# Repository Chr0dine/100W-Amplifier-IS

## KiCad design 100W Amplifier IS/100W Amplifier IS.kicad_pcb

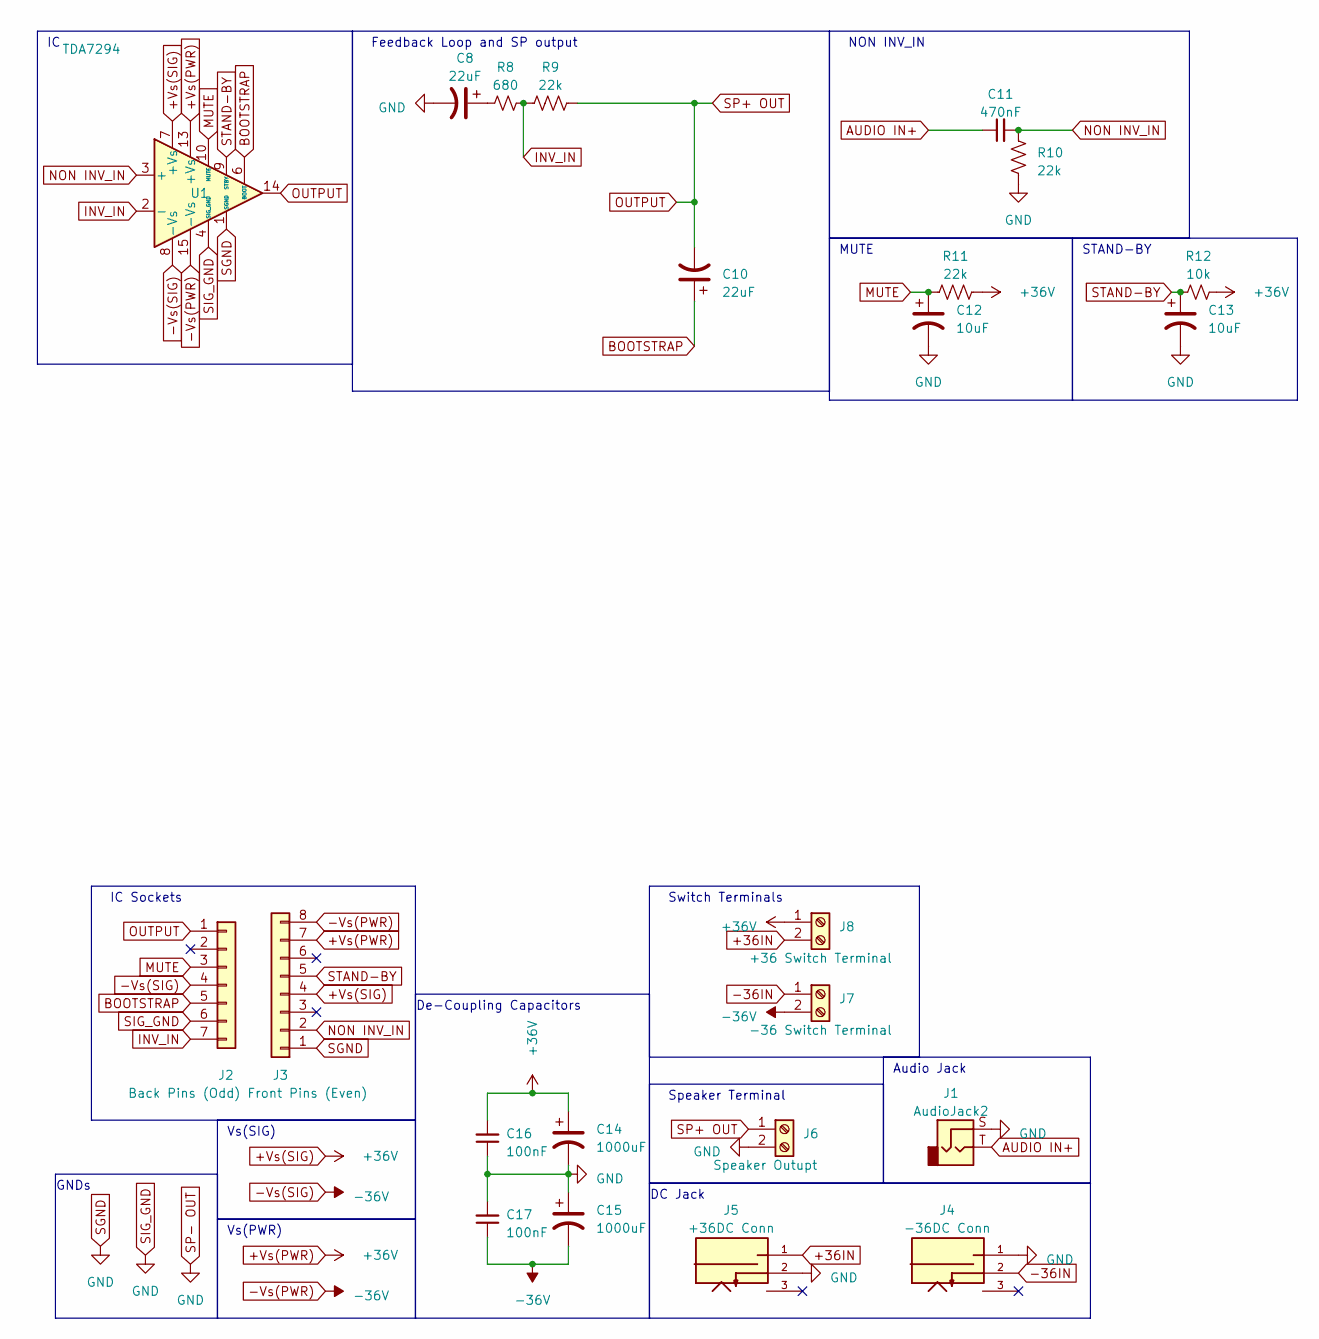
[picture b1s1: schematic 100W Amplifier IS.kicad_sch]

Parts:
C8, C10: 22uF; CP_Radial_D10.0mm_P5.00mm
C11: 470nF; C_Disc_D5.0mm_W2.5mm_P5.00mm
C12, C13: 10uF; CP_Radial_D8.0mm_P3.50mm
C14, C15: 1000uF; CP_Radial_D16.0mm_P7.50mm
C16, C17: 100nF; C_Disc_D5.0mm_W2.5mm_P5.00mm
J1: AudioJack2; Jack_3.5mm_CUI_SJ1-3523N_Horizontal
J2: Back Pins (Odd); PinSocket_1x07_P2.54mm_Vertical
J3: Front Pins (Even); PinSocket_1x08_P2.54mm_Vertical
J4: -36DC Conn; GRAVITECH_CON-SOCJ-2155; PARTREV NA
J5: +36DC Conn; GRAVITECH_CON-SOCJ-2155; PARTREV NA
J6: Speaker Outupt; TerminalBlock_Altech_AK300-2_P5.00mm
J7: -36 Switch Terminal; TerminalBlock_Altech_AK300-2_P5.00mm
J8: +36 Switch Terminal; TerminalBlock_Altech_AK300-2_P5.00mm
R8: 680; R_Axial_DIN0207_L6.3mm_D2.5mm_P10.16mm_Horizontal
R9, R10, R11: 22k; R_Axial_DIN0207_L6.3mm_D2.5mm_P10.16mm_Horizontal
R12: 10k; R_Axial_DIN0207_L6.3mm_D2.5mm_P10.16mm_Horizontal
U1: TDA7294

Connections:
+36IN: J5.1, J8.2
+Vs(PWR): C14.1, C16.2, J3.4, J3.7, J8.1, R11.1, R12.1, U1.7 (+Vs), U1.13 (+Vs)
-36IN: J4.2, J7.1
-Vs(PWR): C15.2, C17.1, J2.4, J3.8, J7.2, U1.8 (-Vs), U1.15 (-Vs)
AUDIO IN+: C11.1, J1.T
BOOTSTRAP: C10.1, J2.5, U1.6 (BOOT)
INV_IN: J2.7, R8.2, R9.1, U1.2 (-)
MUTE: C12.1, J2.3, R11.2, U1.10 (MUTE)
NON INV_IN: C11.2, J3.2, R10.2, U1.3 (+)
unnamed: C8.1, R8.1
OUTPUT: C10.2, J2.1, J6.1, R9.2, U1.14
SGND: C8.2, C12.2, C13.2, C14.2, C15.1, C16.1, C17.2, J1.S, J2.6, J3.1, J4.1, J5.2, J6.2, R10.1, U1.1 (SGND), U1.4 (SIG_GND)
STAND-BY: C13.1, J3.5, R12.2, U1.9 (STBY)

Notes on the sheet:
Vs(PWR)
DC Jack
GNDs
MUTE
Switch Terminals
STAND-BY
NON INV_IN
Speaker Terminal
Audio Jack
De-Coupling Capacitors
IC Sockets
Feedback Loop and SP output
Vs(SIG)

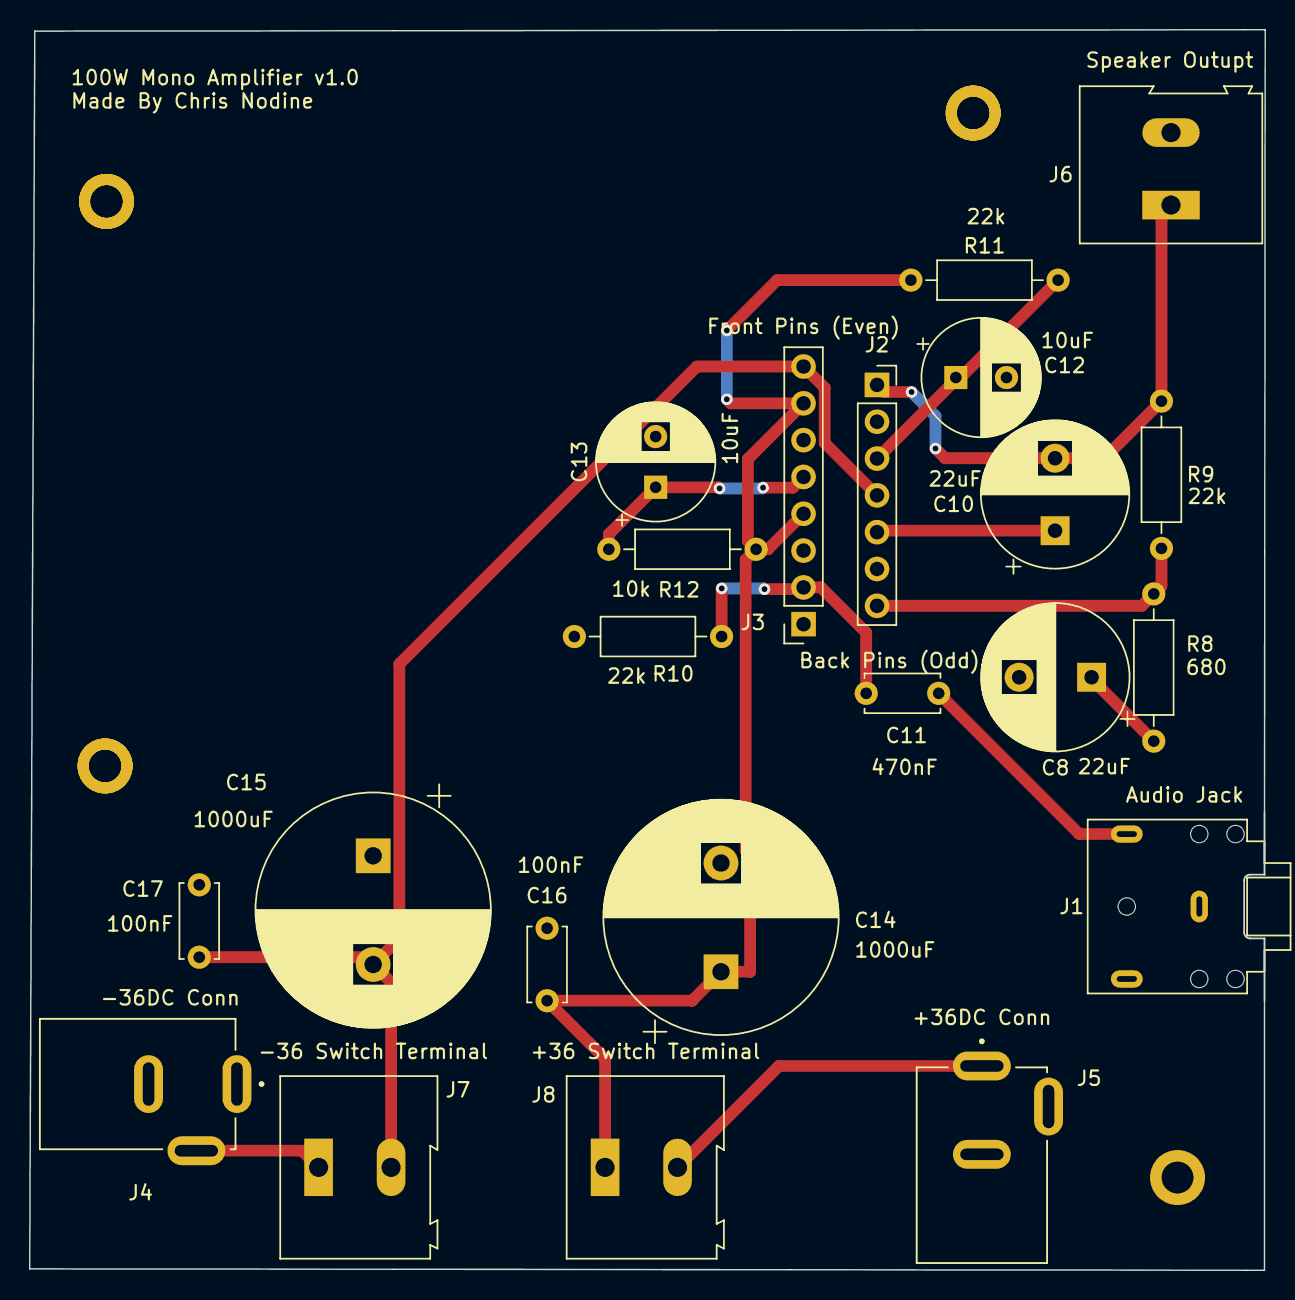
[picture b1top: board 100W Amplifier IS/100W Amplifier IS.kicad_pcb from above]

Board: 2 copper layers, 85.2 x 85.6 mm, 22 parts (0 on the bottom side), 13 nets.

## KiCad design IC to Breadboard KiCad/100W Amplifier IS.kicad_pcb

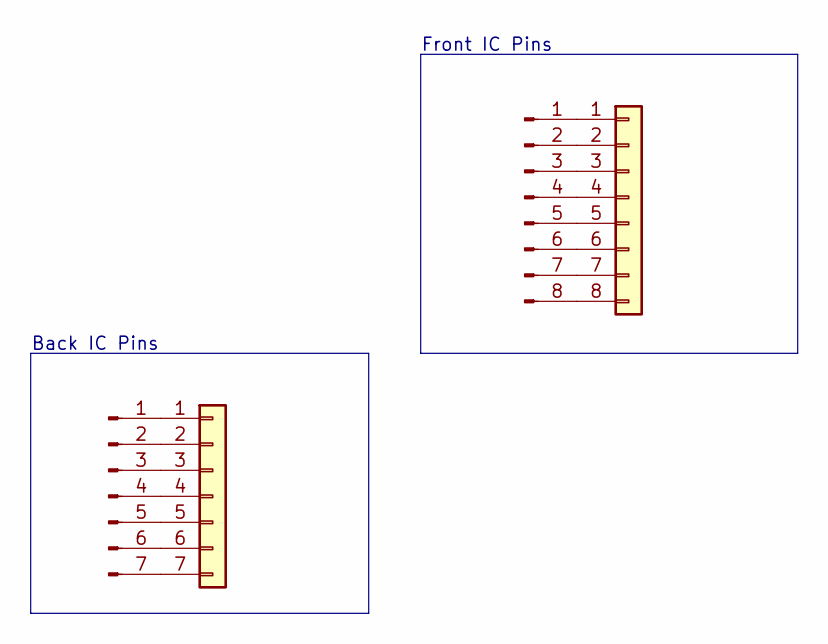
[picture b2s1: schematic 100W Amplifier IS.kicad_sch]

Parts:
J1: Conn_01x08; PinSocket_1x08_P2.54mm_Vertical
J2: Conn_01x07_Pin; PinHeader_1x07_P2.54mm_Vertical
J3: Conn_01x08_Pin; PinHeader_1x08_P2.54mm_Vertical
J4: Conn_01x07; PinSocket_1x07_P2.54mm_Vertical

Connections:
unnamed: J1.1, J3.1
unnamed: J1.2, J3.2
unnamed: J1.3, J3.3
unnamed: J1.4, J3.4
unnamed: J1.5, J3.5
unnamed: J1.6, J3.6
unnamed: J1.7, J3.7
unnamed: J1.8, J3.8
unnamed: J2.1, J4.1
unnamed: J2.2, J4.2
unnamed: J2.3, J4.3
unnamed: J2.4, J4.4
unnamed: J2.5, J4.5
unnamed: J2.6, J4.6
unnamed: J2.7, J4.7

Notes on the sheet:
Back IC Pins
Front IC Pins

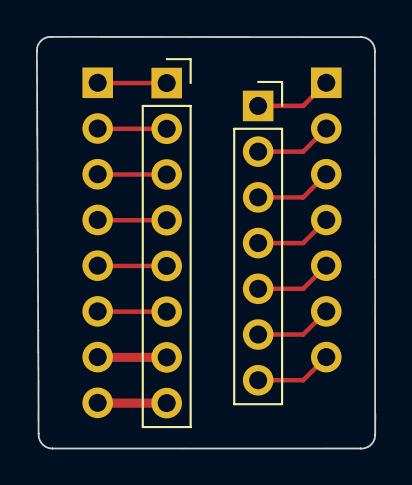
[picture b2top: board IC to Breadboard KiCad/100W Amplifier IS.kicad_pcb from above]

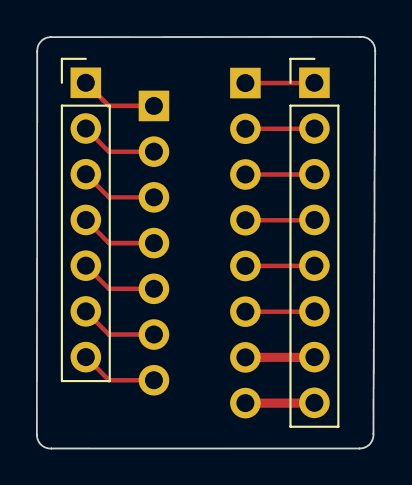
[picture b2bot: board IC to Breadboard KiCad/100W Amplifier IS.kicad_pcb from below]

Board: 2 copper layers, 18.8 x 22.9 mm, 4 parts (2 on the bottom side), 15 nets.

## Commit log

2023-04-16 Adapter Schematics
2023-04-18 Adding Falstad Diagram
2023-05-02 KiCad Schematic and updated resources
2023-05-17 New Circuit and KiCad PCB Completed
2023-06-15 gerber files
